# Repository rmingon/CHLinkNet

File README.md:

# CH32V307 Ethernet + PoE Development Board

## Overview

This project is a **custom 4-layer development board** based on the **WCH CH32V307RCT6** RISC-V microcontroller.  
It integrates **Ethernet connectivity**, **USB programming**, and **Power-over-Ethernet (PoE) readiness** through an external module header.

The design was fully created in **KiCad 9.0.3**, including schematic, PCB layout, and 3D mechanical validation.

---

## Key Features

- **MCU:** WCH **CH32V307RCT6**

  - 32-bit RISC-V core @144 MHz
  - 256 KB Flash / 64 KB SRAM
  - Integrated MAC controller for Ethernet
  - USB 2.0 Full-Speed, CAN, ADC, PWM, and multiple GPIOs

- **Ethernet Interface:**

  - **HY931147C** RJ45 connector with integrated magnetics and LEDs
  - RMII interface connected to the CH32V307 MAC peripheral
  - Differential pair routing with impedance control for signal integrity

- **USB Interface:**

  - Micro-USB Type-B connector (J1)
  - **CH340C** USB-to-UART converter for serial programming/debugging
  - USB-powered operation (5 V input)

- **Power Supply:**

  - Input: **5 V** from USB or external PoE module (J3)
  - **LM1117-3.3V** linear regulator provides system 3.3 V rail
  - PoE header allows integration of a DC-DC converter (48 V → 5 V)

- **Clock System:**

  - **25 MHz crystal** (Y1) with 10 pF load capacitors
  - Supports both internal and external oscillators

- **Programming and Debugging:**

  - **1×8 header (J2)** for SWD and UART interface
  - **JP1** (BOOT0) and **JP2** (BOOT1) jumpers for boot mode selection
  - Compatible with WCHISPTool and OpenOCD

- **Status Indicators:**

  - Power LED
  - Dual user LEDs (green and yellow) connected via GPIOs with current-limiting resistors

- **PCB Details:**
  - **4-layer stack-up:**
    - Top: Signal
    - Inner 1: GND plane
    - Inner 2: 3V3 power plane
    - Bottom: Signal
  - Controlled impedance routing for RMII
  - Ground pour under high-speed signals for noise reduction
  - Rounded corners, compact form factor, and 3D-verified mechanical fit

---

## Hardware Architecture

### Power Section

- **Primary Source:** USB 5 V from J1
- **Secondary Source:** PoE module input via J3 header
- **Voltage Regulation:**
  - U3 (LM1117-3.3V) converts 5 V → 3.3 V
  - C4–C6 ensure low-noise decoupling near MCU and PHY
  - Separate power planes on inner layers for 3.3 V and 5 V distribution

### Ethernet Section

- **U1: HY931147C RJ45 connector** with built-in magnetics
- Connected to MCU’s RMII interface pins (TXD, RXD, CRS, REF_CLK, etc.)
- Controlled-impedance differential pairs routed on top layer, referenced to inner GND plane
- Shield and chassis ground isolated via filtering for EMI reduction

### USB-to-UART Interface

- **U4: CH340C** converts USB signals to UART for MCU programming
- Connected to TX_PROG and RX_PROG pins on CH32V307
- Includes pull-up and filtering capacitors for reliable USB operation

### Clock and Reset Circuit

- **Y1: 25 MHz crystal** connected to OSC_IN/OSC_OUT
- **JP1/JP2 jumpers** configure MCU boot mode (Flash, System Memory, SRAM)
- **NRST pin** accessible via programming header (J2)

### Programming Header (J2)

| Pin | Signal   | Description     |
| :-- | :------- | :-------------- |
| 1   | GND      | Ground          |
| 2   | +3V3     | Power reference |
| 3   | RST      | MCU Reset       |
| 4   | RX_PROG  | UART RX         |
| 5   | TX_PROG  | UART TX         |
| 6   | SWCLK    | SWD Clock       |
| 7   | SWDIO    | SWD Data        |
| 8   | NC / RES | Reserved        |

---

## PCB Layout Highlights

- **4-layer design** with solid GND plane and 3V3 power plane
- **Short and symmetric differential routing** for Ethernet and USB signals
- **Via stitching** used to maintain continuous ground reference around high-speed nets
- **Thermal reliefs** on power pads for manufacturability
- **Decoupling capacitors** placed directly next to MCU VDD and PHY pins
- **RJ45 positioned at board edge** for easy cable insertion and mechanical stability

---

## Software & Toolchain

- **Toolchain:**

  - [WCH RISC-V GCC](https://www.wch.cn/downloads/CH32V307.html)
  - [WCHISPTool](https://www.wch.cn/downloads/WCHISPTool.html)
  - [MounRiver Studio](https://www.mounriver.com/)
  - Optional: [OpenOCD](https://openocd.org/) for SWD programming

- **Boot Modes:**
  | BOOT0 | BOOT1 | Boot Mode |
  |:------|:------|:-----------|
  | 0 | 0 | Boot from Flash |
  | 1 | 0 | Boot from System Memory (USB/UART bootloader) |
  | 0 | 1 | Boot from SRAM |

- **Programming Interfaces:**
  - Via USB (CH340C)
  - Via SWD header (J2) using a WCH-Link, J-Link, or OpenOCD adapter

---

## Design Considerations

- Ethernet differential pairs tuned to **50 Ω single-ended / 100 Ω differential impedance**
- Separate **power and ground planes** to minimize noise coupling
- **Short return paths** for high-speed signals
- **ESD protection** recommended on USB and RJ45 lines in next revision
- Provision for **PoE DC-DC converter module** (48 V → 3.3 V)

---

## Future Improvements

- Integrate **onboard PoE power converter**
- Add **ESD suppression arrays** on USB/Ethernet ports
- Replace LM1117 with a **buck converter** for improved efficiency
- Add **test points** for easier debugging and signal probing

---

## License

This project is released under the **CERN Open Hardware License – Strongly Reciprocal (CERN-OHL-S v2)**.  
You are free to study, modify, produce, and distribute this design, provided derivatives remain open-source under the same license.

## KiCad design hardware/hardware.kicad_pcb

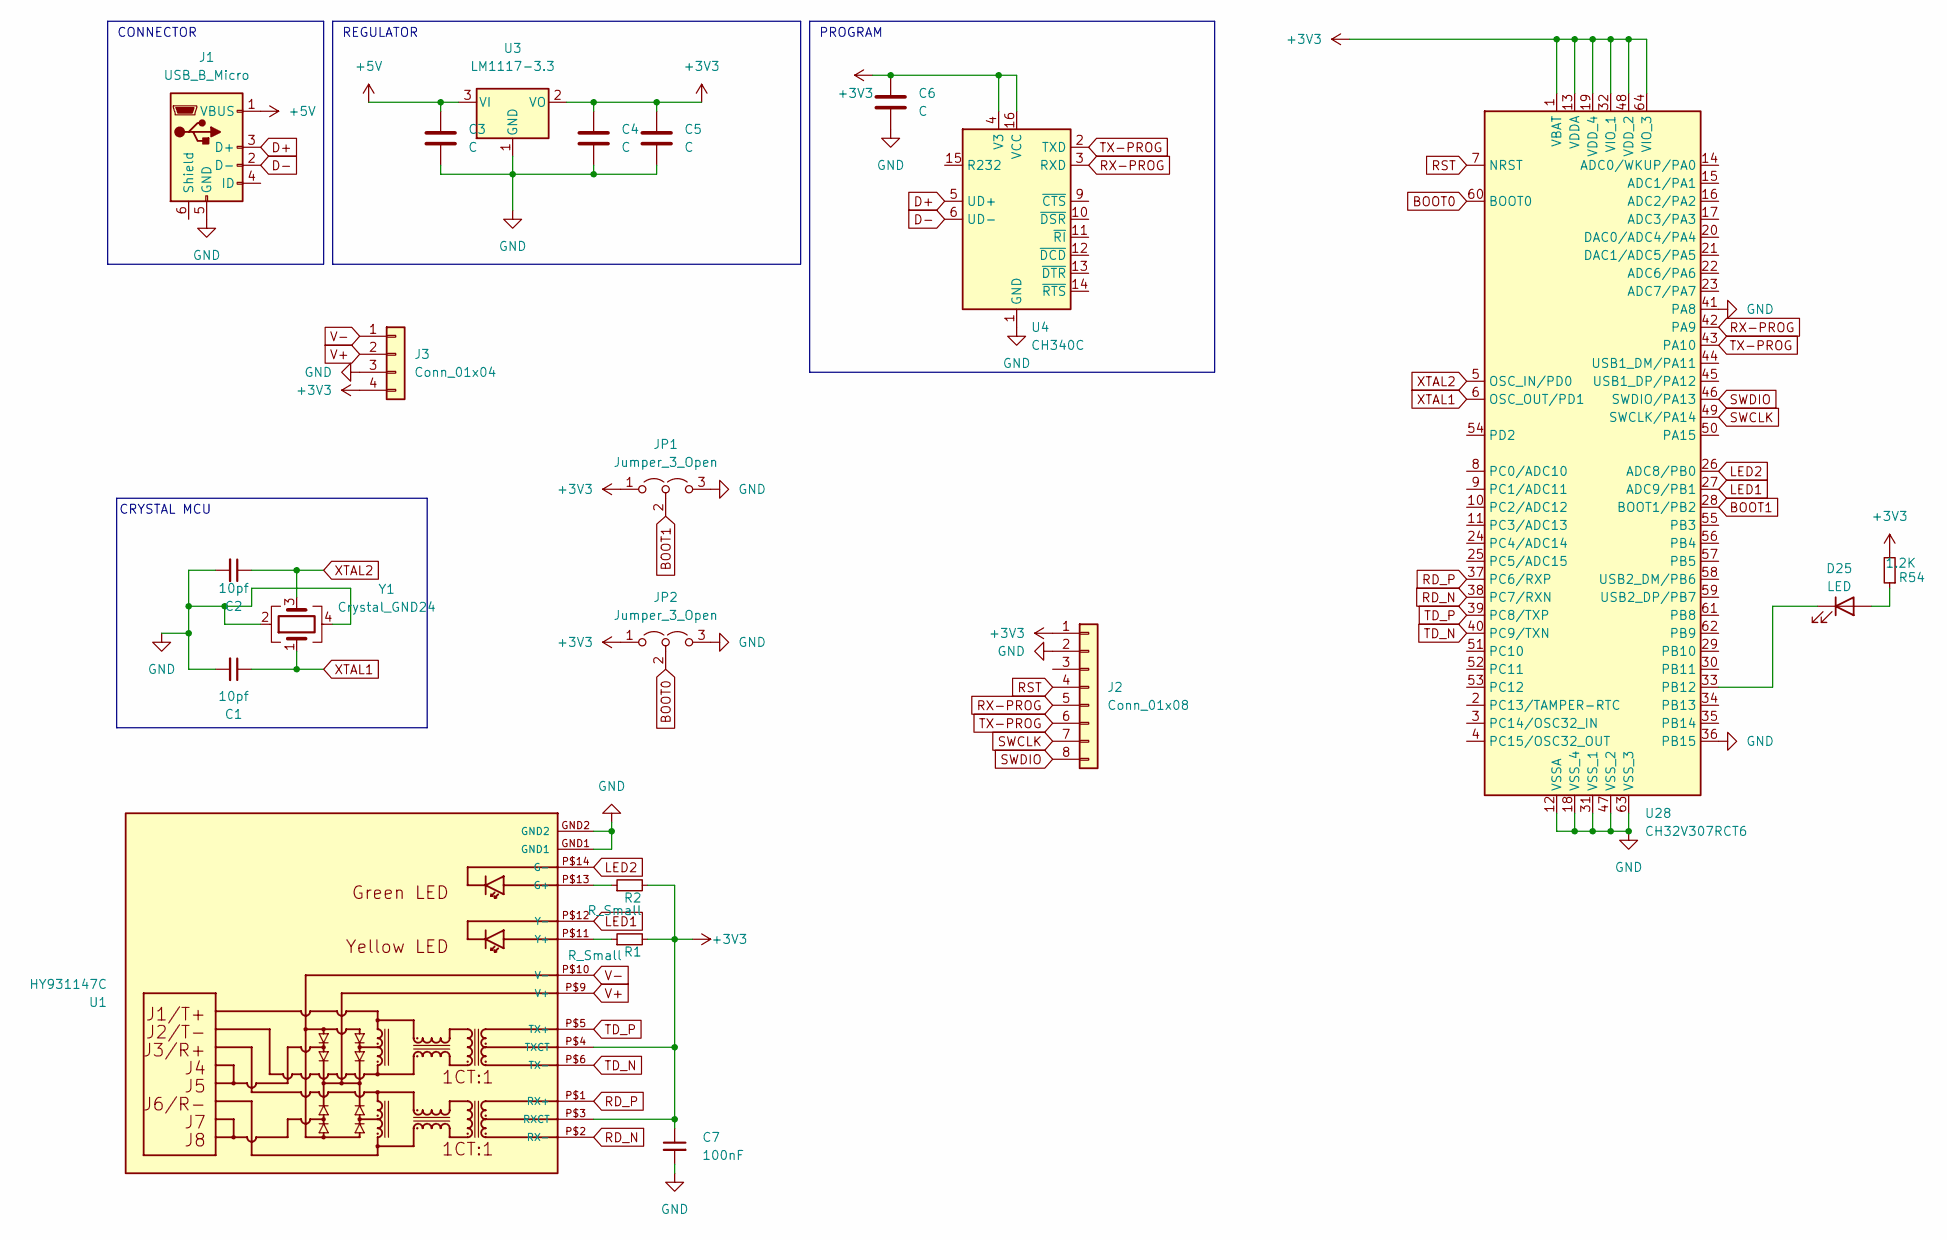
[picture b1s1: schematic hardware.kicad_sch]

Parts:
C1, C2: 10pf; C_0603_1608Metric; LCSC C1634
C3, C4: C; C_0603_1608Metric; LCSC C14663
C5, C6: C; C_0603_1608Metric; LCSC C15849
C7: 100nF; C_0603_1608Metric; LCSC C1634
D25: LED; LED_0603_1608Metric
J1: USB_B_Micro; USB_Micro-B_Amphenol_10118194_Horizontal; LCSC C132563
J2: Conn_01x08; JST_SH_BM08B-SRSS-TB_1x08-1MP_P1.00mm_Vertical
J3: Conn_01x04; PinHeader_1x04_P2.54mm_Vertical
JP1, JP2: Jumper_3_Open; SolderJumper-3_P1.3mm_Open_RoundedPad1.0x1.5mm
R1, R2: R_Small; R_0603_1608Metric; LCSC C2906976
R54: 1.2K; R_0603_1608Metric; LCSC C2906976
U1: HY931147C
U3: LM1117-3.3; SOT-223-3_TabPin2; LCSC C9662
U4: CH340C; SOIC-16_3.9x9.9mm_P1.27mm; LCSC C84681
U28: CH32V307RCT6; LQFP-64_10x10mm_P0.5mm; LCSC C2988083
Y1: Crystal_GND24; Crystal_SMD_3225-4Pin_3.2x2.5mm_HandSoldering; LCSC C9006

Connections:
+3V3: C4.1, C5.1, C6.1, C7.1, J2.1, J3.4, JP1.1 (A), JP2.1 (A), R1.2, R2.2, R54.2, U1.P$3 (RXCT), U1.P$4 (TXCT), U3.2 (VO), U4.4 (V3), U4.16 (VCC), U28.1 (VBAT), U28.13 (VDDA), U28.19 (VDD_4), U28.32 (VIO_1), U28.48 (VDD_2), U28.64 (VIO_3)
+5V: C3.1, J1.1 (VBUS), U3.3 (VI)
BOOT0: JP2.2 (C), U28.60 (BOOT0)
BOOT1: JP1.2 (C), U28.28 (BOOT1/PB2)
D+: J1.3 (D+), U4.5 (UD+)
D-: J1.2 (D-), U4.6 (UD-)
GND: C1.2, C2.2, C3.2, C4.2, C5.2, C6.2, C7.2, J1.5 (GND), J2.2, J3.3, JP1.3 (B), JP2.3 (B), U1.GND1, U1.GND2, U3.1 (GND), U4.1 (GND), U28.12 (VSSA), U28.18 (VSS_4), U28.31 (VSS_1), U28.36 (PB15), U28.41 (PA8), U28.47 (VSS_2), U28.63 (VSS_3), Y1.2, Y1.4
LED1: U1.P$12 (Y-), U28.27 (ADC9/PB1)
LED2: U1.P$14 (G-), U28.26 (ADC8/PB0)
unnamed: D25.2 (A), R54.1
unnamed: D25.1 (K), U28.33 (PB12)
unnamed: R2.1, U1.P$13 (G+)
unnamed: R1.1, U1.P$11 (Y+)
RD_N: U1.P$2 (RX-), U28.38 (PC7/RXN)
RD_P: U1.P$1 (RX+), U28.37 (PC6/RXP)
RST: J2.4, U28.7 (NRST)
RX-PROG: J2.5, U4.3 (RXD), U28.42 (PA9)
SWCLK: J2.7, U28.49 (SWCLK/PA14)
SWDIO: J2.8, U28.46 (SWDIO/PA13)
TD_N: U1.P$6 (TX-), U28.40 (PC9/TXN)
TD_P: U1.P$5 (TX+), U28.39 (PC8/TXP)
TX-PROG: J2.6, U4.2 (TXD), U28.43 (PA10)
V+: J3.2, U1.P$9 (V+)
V-: J3.1, U1.P$10 (V-)
XTAL1: C1.1, U28.6 (OSC_OUT/PD1), Y1.1
XTAL2: C2.1, U28.5 (OSC_IN/PD0), Y1.3

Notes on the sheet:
CRYSTAL MCU
PROGRAM
CONNECTOR
REGULATOR

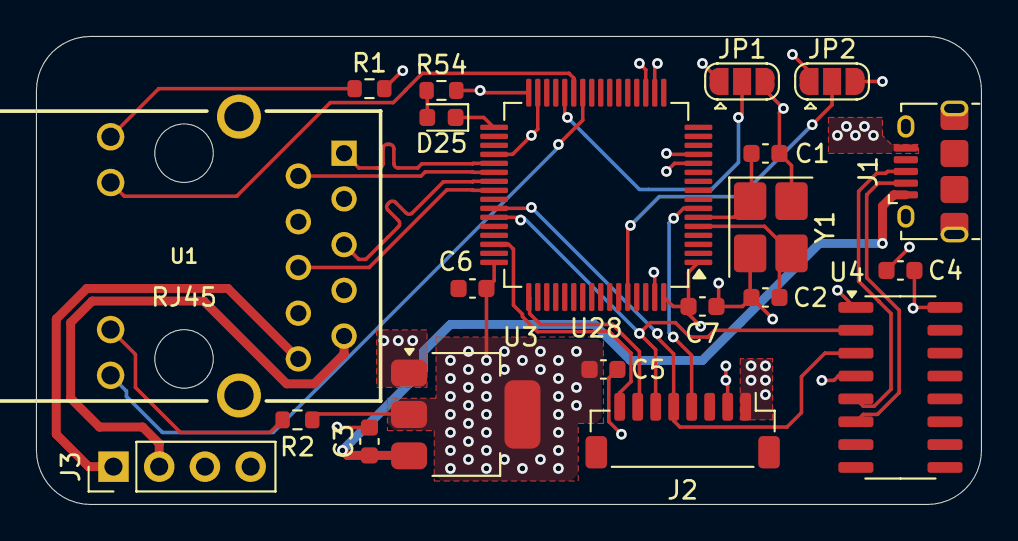
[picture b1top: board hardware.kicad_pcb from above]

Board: 4 copper layers, 52.5 x 26.0 mm, 21 parts (0 on the bottom side), 26 nets.

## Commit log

2025-10-05 add minimal schematic
2025-10-06 differencial wiring
2025-10-07 wiring pcb
2025-10-07 add pictures
2025-10-07 add readme
2025-10-07 add licence
